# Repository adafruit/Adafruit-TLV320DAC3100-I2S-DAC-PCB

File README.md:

## Adafruit TLV320DAC3100 I2S DAC with Headphone and Speaker Out PCB

<a href="http://www.adafruit.com/products/6309"><br/>
Click here to purchase one from the Adafruit shop</a>

PCB files for the Adafruit TLV320DAC3100 I2S DAC with Headphone and Speaker Out. 

Format is EagleCAD schematic and board layout
* https://www.adafruit.com/product/6309

### Description

We stock a lot of chips and development boards that are able to do high quality digital I2S out, which makes for great quality audio playback. That's great when you have enough processing power to decode WAVs or MP3s in real time. However, most give you stereo line-out which cannot connect to head-phones...until now!

We really love the sounds coming out of the Adafruit TLV320DAC3100 I2S DAC with Stereo Headphone and Mono Speaker output - it's got clean, excellent-quality, stereo audio that can connect directly to your 16Ω headphones and/or a 4Ω-8Ω speaker. This makes it excellent for all-in-one audio projects without needing an external amplifier. Please note that while it does not need a MCLK signal (you can configure it to use BCLK as the PLL input) it does require I2C configuration! You will need a microcontroller with our library (Arduino, CircuitPython or Python) to set up the board for audio playback.

This breakout makes amplified I2S digital audio easy. You can power it with 3V (headphone only) or 5VDC (for speaker support) and provide BCLK (bit clock), WSEL (left/right word select), and DIN (data in). Then configure the board with I2C to determine the gain and which output you want activated. There's tons of configuration options available, but we've used it mostly for 16-bit I2S audio. There's a built-in PLL that will generate an MCLK signal from BCLK for you so it can be used by any I2S source.

Audio output from the headphone is AC-coupled. Audio from the speaker is a class-D amplifier and must be connected to a speaker only. If you need an external amplifier, use the headphone jack. 

There's a few extra breakouts on this board: MIC and BIAS are connected to the 'fourth' contact on headsets that often have a microphone. You can configure the amp to provide a 2V bias voltage which will let you detect when a headset+mic is plugged in, and also detect when the headset button is pressed. There's also AIN1/AIN2 which are alternative mix-ins for the audio outputs, not I2S encoders. There is one 'GPIO' pin which can also be used as an IRQ line.

Note that this board can be powered from 3~5VDC but all logic level is 3.3V only (it's quite rare for an I2S microcontroller/computer to have 5V logic!)

Each order comes with one Adafruit TLV320DAC3100 DAC breakout and some header you can solder on for breadboard usage.

### License

Adafruit invests time and resources providing this open source design, please support Adafruit and open-source hardware by purchasing products from [Adafruit](https://www.adafruit.com)!

Designed by Limor Fried/Ladyada for Adafruit Industries.

Creative Commons Attribution/Share-Alike, all text above must be included in any redistribution. 
See license.txt for additional details.

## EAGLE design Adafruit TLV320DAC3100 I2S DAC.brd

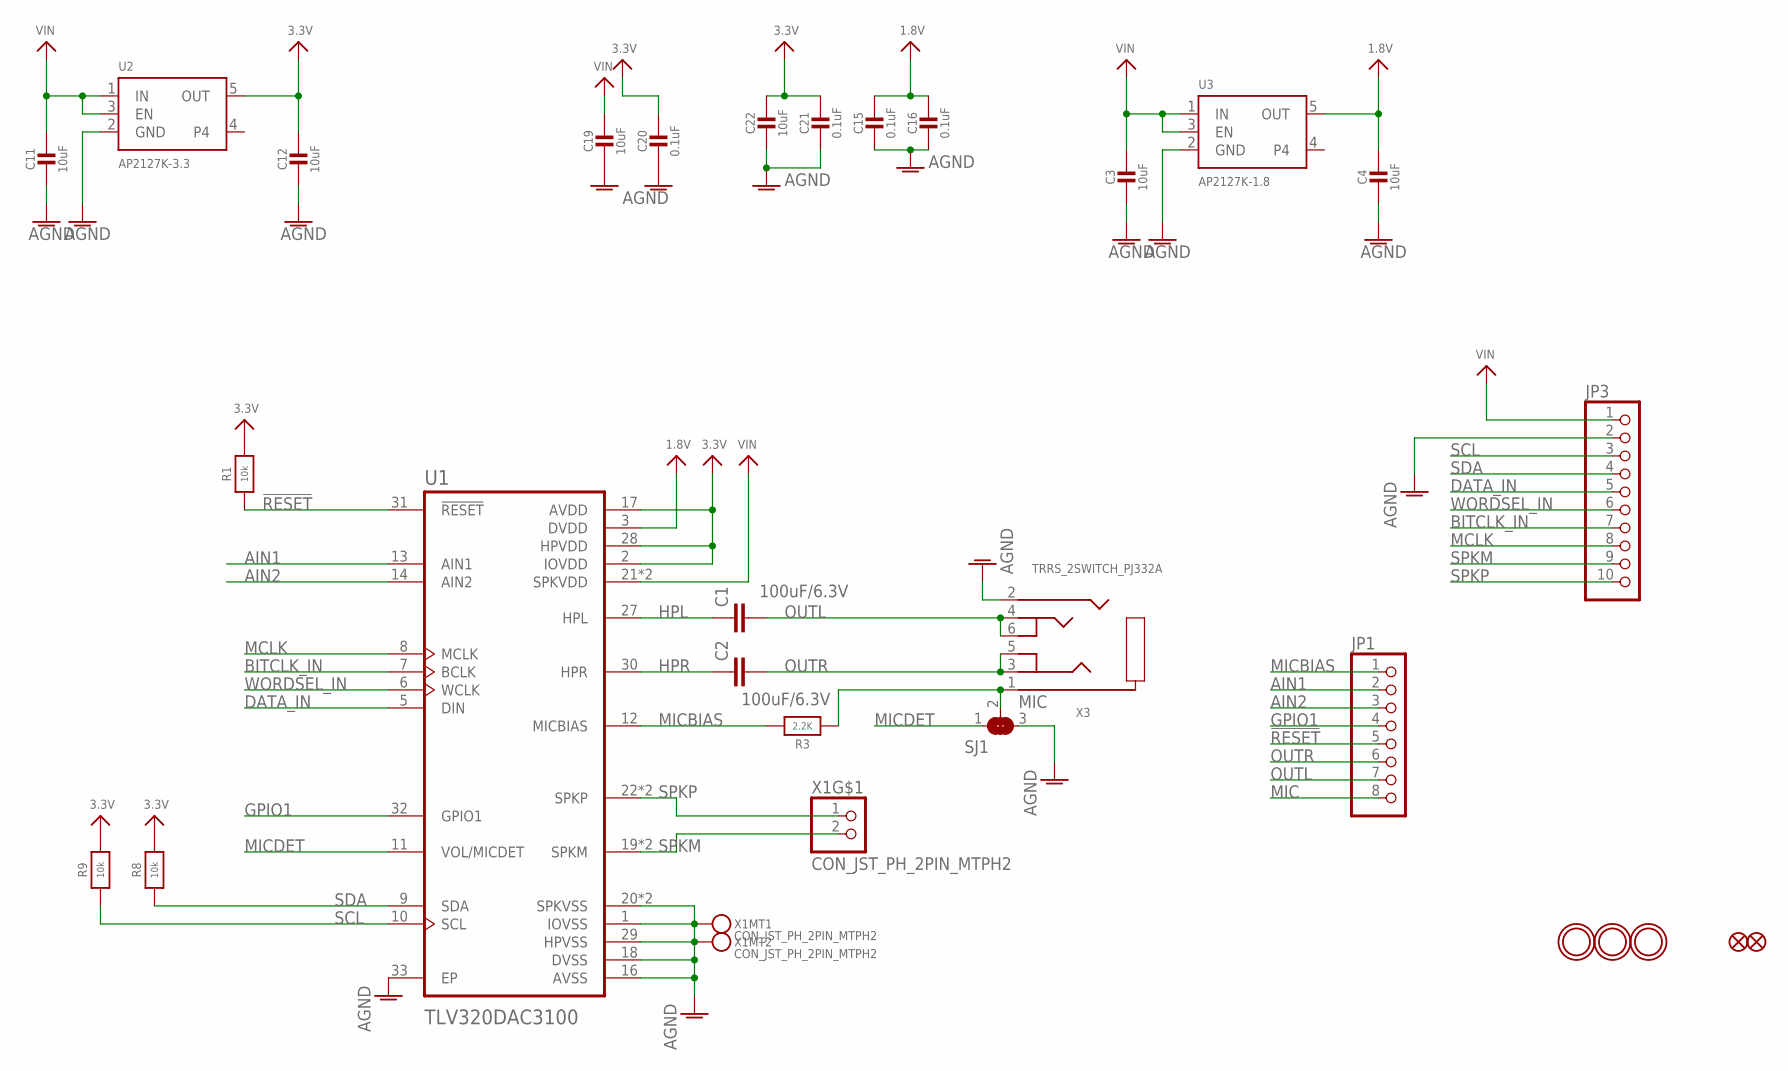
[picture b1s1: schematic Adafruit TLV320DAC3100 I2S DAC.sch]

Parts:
C1, C2: 100uF/6.3V; C1210
C3, C4, C11, C12, C19, C22: 10uF; 0805-NO
C15, C16, C20, C21: 0.1uF; 0603-NO
FID1, FID2: FIDUCIAL_0.5MM
JP1: HEADER-1X870MIL; 1X08_ROUND_70
JP3: HEADER-1X1070MIL; 1X10_ROUND70
R1, R8, R9: 10k; 0603-NO
R3: 2.2K; 0603-NO
SJ1: SOLDERJUMPER_2WAY; SOLDERJUMPER_2WAY_OPEN_NOPASTE
U1: TLV320DAC3100
U2: AP2127K-3.3; SOT23-5
U3: AP2127K-1.8; SOT23-5
U$12, U$13, U$14: MOUNTINGHOLE2.5; MOUNTINGHOLE_2.5_PLATED
X1: CON_JST_PH_2PIN_MTPH2; JSTPH2
X3: TRRS_2SWITCH_PJ332A; PJ-332A

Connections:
1.8V: C4.1, C15.1, C16.1, U1.3 (DVDD), U3.5 (OUT)
3.3V: C12.1, C20.1, C21.1, C22.1, R1.2, R8.2, R9.2, U1.2 (IOVDD), U1.17 (AVDD), U1.28 (HPVDD), U2.5 (OUT)
!RESET: JP1.5, R1.1, U1.31 (!RESET)
AGND: C3.2, C4.2, C11.2, C12.2, C15.2, C16.2, C19.2, C20.2, C21.2, C22.2, JP3.2, SJ1.3, U1.1 (IOVSS), U1.16 (AVSS), U1.18 (DVSS), U1.20 (SPKVSS), U1.25 (SPKVSS), U1.29 (HPVSS), U1.33 (EP), U2.2 (GND), U3.2 (GND), X1.NC1, X1.NC2, X3.2 (RING1)
AIN1: JP1.2, U1.13 (AIN1)
AIN2: JP1.3, U1.14 (AIN2)
BITCLK_IN: JP3.7, U1.7 (BCLK)
DATA_IN: JP3.5, U1.5 (DIN)
GPIO1: JP1.4, U1.32 (GPIO1)
HPL: C1.1, U1.27 (HPL)
HPR: C2.1, U1.30 (HPR)
MCLK: JP3.8, U1.8 (MCLK)
MIC: JP1.8, R3.1, SJ1.2, X3.1 (RING)
MICBIAS: JP1.1, R3.2, U1.12 (MICBIAS)
MICDET: SJ1.1, U1.11 (VOL/MICDET)
OUTL: C1.2, JP1.7, X3.4 (TIP), X3.6 (TIP_SW)
OUTR: C2.2, JP1.6, X3.3 (RING2), X3.5 (R2_SW)
SCL: JP3.3, R9.1, U1.10 (SCL)
SDA: JP3.4, R8.1, U1.9 (SDA)
SPKM: JP3.9, U1.19 (SPKM), U1.23 (SPKM), X1.2
SPKP: JP3.10, U1.22 (SPKP), U1.26 (SPKP), X1.1
VIN: C3.1, C11.1, C19.1, JP3.1, U1.21 (SPKVDD), U1.24 (SPKVDD), U2.1 (IN), U2.3 (EN), U3.1 (IN), U3.3 (EN)
WORDSEL_IN: JP3.6, U1.6 (WCLK)

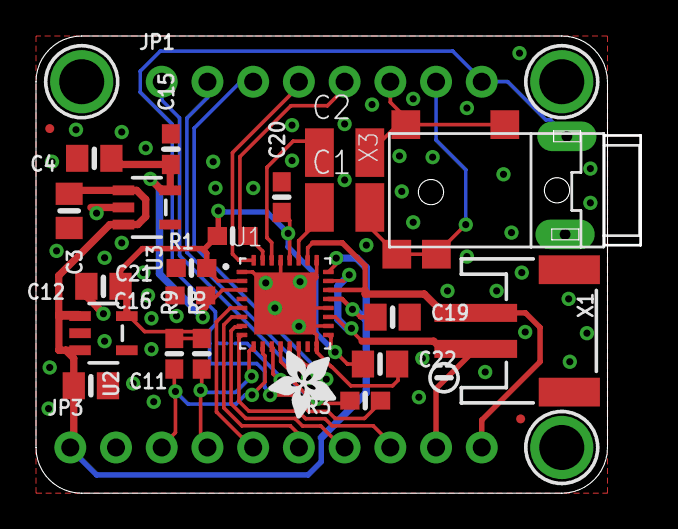
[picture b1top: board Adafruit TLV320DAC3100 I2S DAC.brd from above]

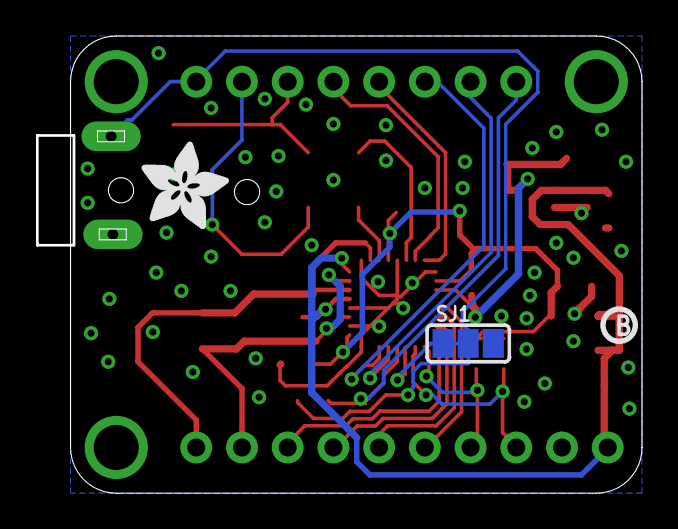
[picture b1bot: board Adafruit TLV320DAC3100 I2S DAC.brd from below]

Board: 2 copper layers, 33.5 x 25.2 mm, 60 parts (10 on the bottom side), 23 nets.

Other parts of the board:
E$1: SYMBOL_MINUS
PLABEL0: PLABEL0
PLABEL1: PLABEL1
PLABEL2: PLABEL2
PLABEL3: PLABEL3
PLABEL4: PLABEL4
PLABEL5: PLABEL5
PLABEL6: PLABEL6
PLABEL7: PLABEL7
PLABEL8: PLABEL8
PLABEL9: PLABEL9
PLABEL10: PLABEL10
PLABEL11: PLABEL11
PLABEL12: PLABEL12
PLABEL13: PLABEL13
PLABEL14: PLABEL14
PLABEL15: PLABEL15
PLABEL16: PLABEL16
PLABEL17: PLABEL17
PLABEL18: PLABEL18
PLABEL19: PLABEL19
PLABEL20: PLABEL20
PLABEL21: PLABEL21
PLABEL22: PLABEL22
PLABEL23: PLABEL23
PLABEL24: PLABEL24
PLABEL25: PLABEL25
PLABEL26: PLABEL26
U$5: PCBFEAT-REV-040
U$6: ADAFRUIT_5MM
U$29: ADAFRUIT_3.5MM

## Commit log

2025-03-27 cookiecutter

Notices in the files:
parts and their libraries:
microbuilder: This work is placed in the public domain, and may be freely used for commercial and non-commercial work with the following conditions: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
